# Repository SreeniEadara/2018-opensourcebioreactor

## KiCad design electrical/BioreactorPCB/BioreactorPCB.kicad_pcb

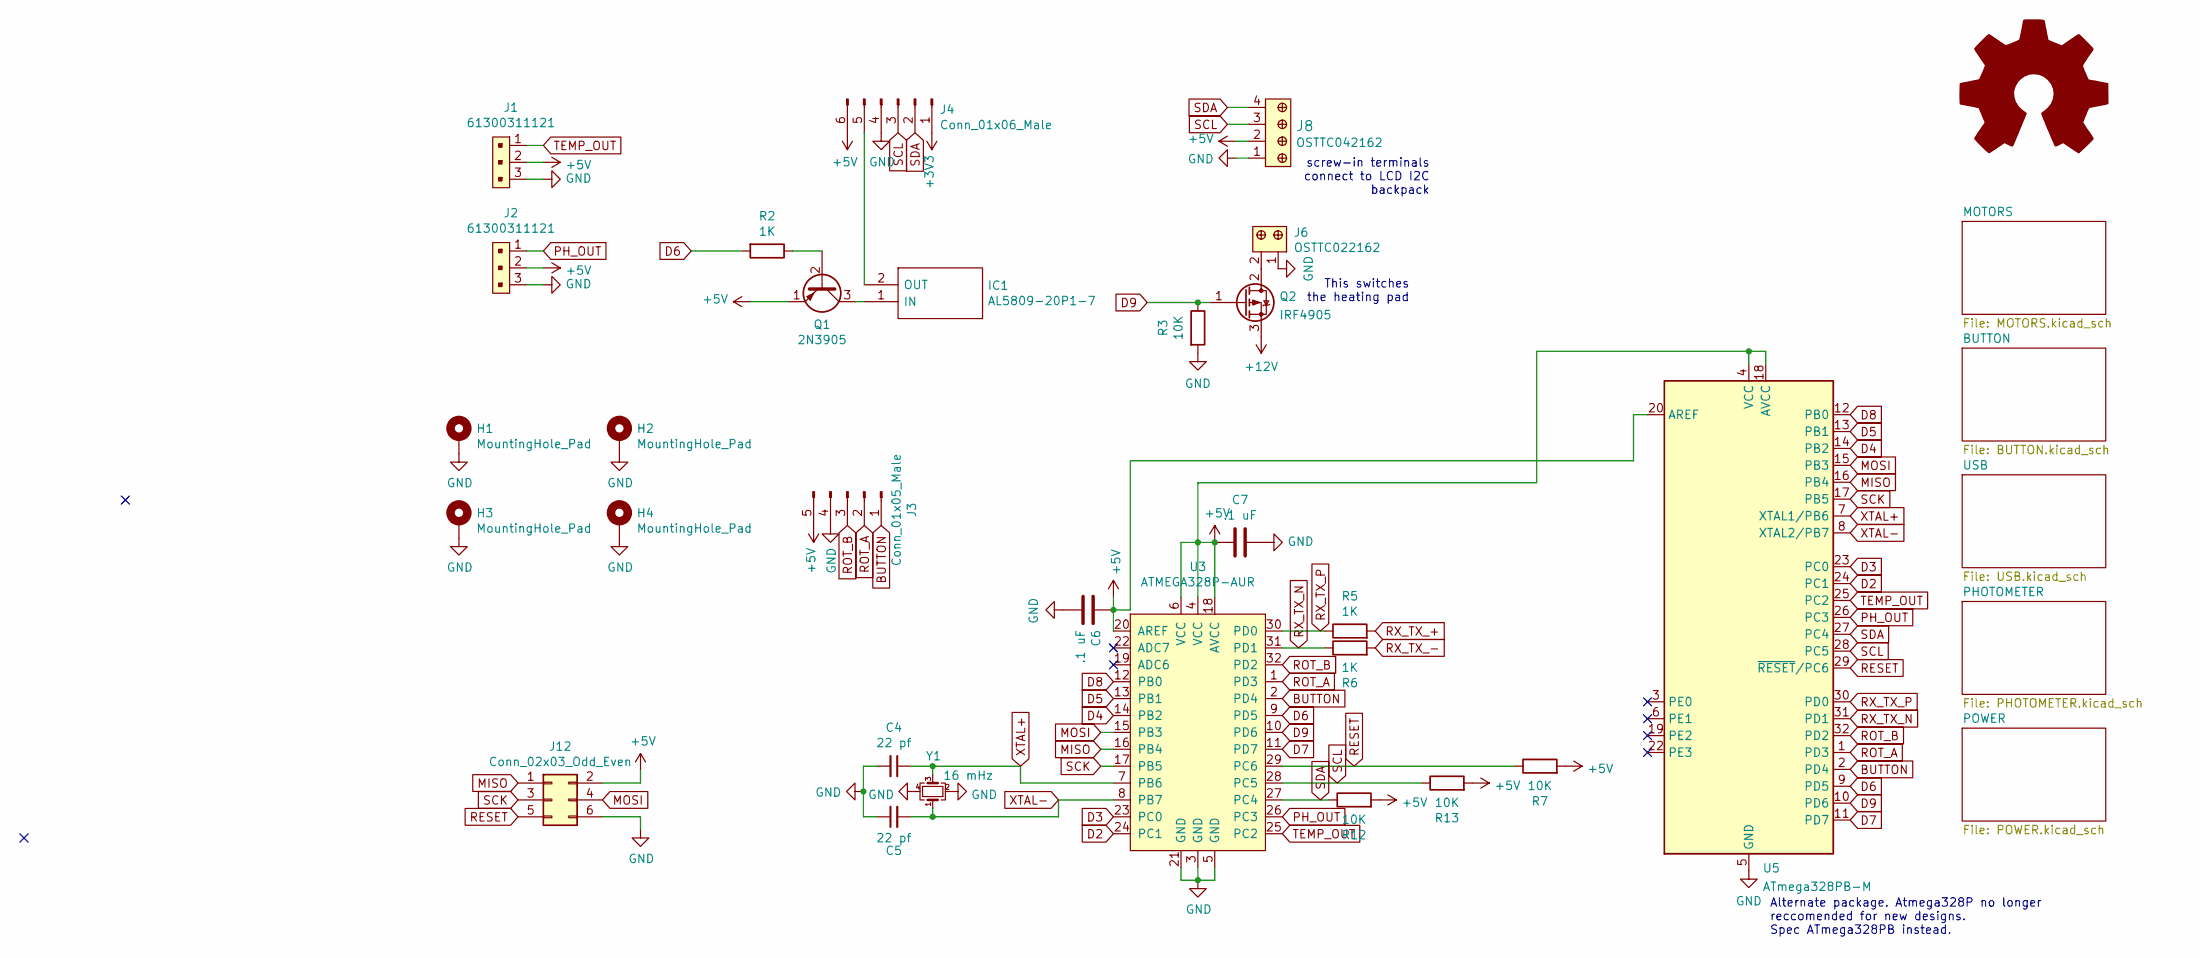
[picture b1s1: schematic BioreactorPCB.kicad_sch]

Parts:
C4, C5: 22 pf; C_0603_1608Metric_Pad1.08x0.95mm_HandSolder
C6, C7: .1 uF; C_0603_1608Metric_Pad1.08x0.95mm_HandSolder
H1, H2, H3, H4: MountingHole_Pad; MountingHole_3.2mm_M3_DIN965_Pad
IC1: AL5809-20P1-7; AL580920QP17; Manufacturer_Part_Number AL5809-20P1-7; Mouser Part Number 621-AL5809-20P1-7
J1, J2: 61300311121; PinHeader_1x3_P2.54_Drill1.1mm; MPN 61300311121; Digi-Key_PN 732-5316-ND
J3: Conn_01x05_Male; Molex_KK-254_AE-6410-05A_1x05_P2.54mm_Vertical
J4: Conn_01x06_Male; Molex_KK-254_AE-6410-06A_1x06_P2.54mm_Vertical
J6: OSTTC022162; Term_Block_1x2_P5.08MM; MPN OSTTC022162; Digi-Key_PN ED2609-ND
J8: OSTTC042162; Term_Block_1x4_P5.08mm; MPN OSTTC042162; Digi-Key_PN ED2611-ND
J12: Conn_02x03_Odd_Even; PinHeader_2x03_P2.54mm_Vertical
Q1: 2N3905; TO-92_Inline
Q2: IRF4905; TO-262-3_Vertical
R2, R5, R6: 1K; R_0805_2012Metric_Pad1.20x1.40mm_HandSolder
R3, R7, R12, R13: 10K; R_0805_2012Metric_Pad1.20x1.40mm_HandSolder
U3: ATMEGA328P-AUR; TQFP-32_7x7mm; MPN ATMEGA328P-AUR; Digi-Key_PN ATMEGA328P-AURCT-ND
U5: ATmega328PB-M; QFN-32-1EP_5x5mm_P0.5mm_EP3.1x3.1mm
Y1: 16 mHz; Crystal_SMD_3225-4Pin_3.2x2.5mm_HandSoldering

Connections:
+3V3: J4.1; also elsewhere on the board
+5V: C6.1, C7.2, J1.2, J2.2, J3.5, J4.6, J8.2, J12.2, Q1.1 (E), R7.2, R12.2, R13.2, U3.4 (VCC), U3.6 (VCC), U3.18 (AVCC), U3.20 (AREF), U5.4 (VCC), U5.18 (AVCC), U5.20 (AREF); also elsewhere on the board
+12V: Q2.3 (S); also elsewhere on the board
BUTTON: J3.1, U3.2 (PD4), U5.2 (PD4)
D2: U3.24 (PC1), U5.24 (PC1); also elsewhere on the board
D3: U3.23 (PC0), U5.23 (PC0); also elsewhere on the board
D4: U3.14 (PB2), U5.14 (PB2); also elsewhere on the board
D5: U3.13 (PB1), U5.13 (PB1); also elsewhere on the board
D6: R2.2, U3.9 (PD5), U5.9 (PD5)
D7: U3.11 (PD7), U5.11 (PD7); also elsewhere on the board
D8: U3.12 (PB0), U5.12 (PB0); also elsewhere on the board
D9: Q2.1 (G), R3.1, U3.10 (PD6), U5.10 (PD6)
GND: C4.2, C5.1, C6.2, C7.1, H1.1, H2.1, H3.1, H4.1, J1.3, J2.3, J3.4, J4.4, J6.1, J8.1, J12.6, R3.2, U3.3 (GND), U3.5 (GND), U3.21 (GND), U5.5 (GND), U5.21 (GND), U5.33 (GND), Y1.2, Y1.4; also elsewhere on the board
MISO: J12.1, U3.16 (PB4), U5.16 (PB4)
MOSI: J12.4, U3.15 (PB3), U5.15 (PB3)
unnamed: IC1.1 (IN), Q1.3 (C)
unnamed: IC1.2 (OUT), J4.5
unnamed: J6.2, Q2.2 (D)
unnamed: Q1.2 (B), R2.1
PH_OUT: J2.1, U3.26 (PC3), U5.26 (PC3)
RESET: J12.5, R7.1, U3.29 (PC6), U5.29 (~RESET/PC6); also elsewhere on the board
ROT_A: J3.2, U3.1 (PD3), U5.1 (PD3)
ROT_B: J3.3, U3.32 (PD2), U5.32 (PD2)
RX_TX_+: R5.2; also elsewhere on the board
RX_TX_-: R6.2; also elsewhere on the board
RX_TX_N: R6.1, U3.31 (PD1), U5.31 (PD1)
RX_TX_P: R5.1, U3.30 (PD0), U5.30 (PD0)
SCK: J12.3, U3.17 (PB5), U5.17 (PB5)
SCL: J4.3, J8.3, R13.1, U3.28 (PC5), U5.28 (PC5)
SDA: J4.2, J8.4, R12.1, U3.27 (PC4), U5.27 (PC4)
TEMP_OUT: J1.1, U3.25 (PC2), U5.25 (PC2)
XTAL+: C4.1, U3.7 (PB6), U5.7 (XTAL1/PB6), Y1.3
XTAL-: C5.2, U3.8 (PB7), U5.8 (XTAL2/PB7), Y1.1

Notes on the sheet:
This switches the heating pad
screw-in terminals connect to LCD I2C backpack
Alternate package. Atmega328P no longer reccomended for new designs. Spec ATmega328PB instead.

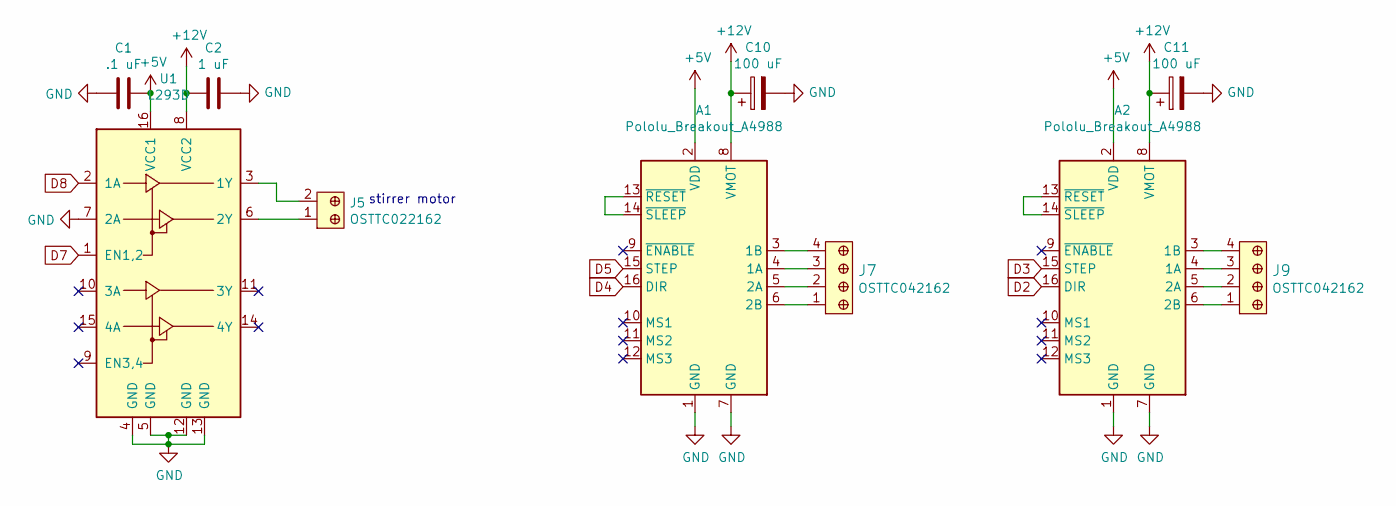
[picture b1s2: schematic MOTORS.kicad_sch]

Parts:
A1, A2: Pololu_Breakout_A4988; Pololu_Breakout-16_15.2x20.3mm
C1: .1 uF; C_0603_1608Metric_Pad1.08x0.95mm_HandSolder
C2: 1 uF; C_0603_1608Metric_Pad1.08x0.95mm_HandSolder
C10, C11: 100 uF; CP_Radial_D5.0mm_P2.50mm
J5: OSTTC022162; Term_Block_1x2_P5.08MM; MPN OSTTC022162; Digi-Key_PN ED2609-ND
J7, J9: OSTTC042162; Term_Block_1x4_P5.08mm; MPN OSTTC042162; Digi-Key_PN ED2611-ND
U1: L293D; DIP-16_W7.62mm

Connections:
+5V: A1.2 (VDD), A2.2 (VDD), C1.1, U1.16 (VCC1); also elsewhere on the board
+12V: A1.8 (VMOT), A2.8 (VMOT), C2.2, C10.1, C11.1, U1.8 (VCC2); also elsewhere on the board
D2: A2.16 (DIR); also elsewhere on the board
D3: A2.15 (STEP); also elsewhere on the board
D4: A1.16 (DIR); also elsewhere on the board
D5: A1.15 (STEP); also elsewhere on the board
D7: U1.1 (EN1,2); also elsewhere on the board
D8: U1.2 (1A); also elsewhere on the board
GND: A1.1 (GND), A1.7 (GND), A2.1 (GND), A2.7 (GND), C1.2, C2.1, C10.2, C11.2, U1.4 (GND), U1.5 (GND), U1.7 (2A), U1.12 (GND), U1.13 (GND); also elsewhere on the board
unnamed: A1.3 (1B), J7.4
unnamed: A1.4 (1A), J7.3
unnamed: A1.5 (2A), J7.2
unnamed: A1.6 (2B), J7.1
unnamed: A1.13 (~RESET), A1.14 (~SLEEP)
unnamed: A2.3 (1B), J9.4
unnamed: A2.4 (1A), J9.3
unnamed: A2.5 (2A), J9.2
unnamed: A2.6 (2B), J9.1
unnamed: A2.13 (~RESET), A2.14 (~SLEEP)
unnamed: J5.1, U1.6 (2Y)
unnamed: J5.2, U1.3 (1Y)

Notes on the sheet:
stirrer motor

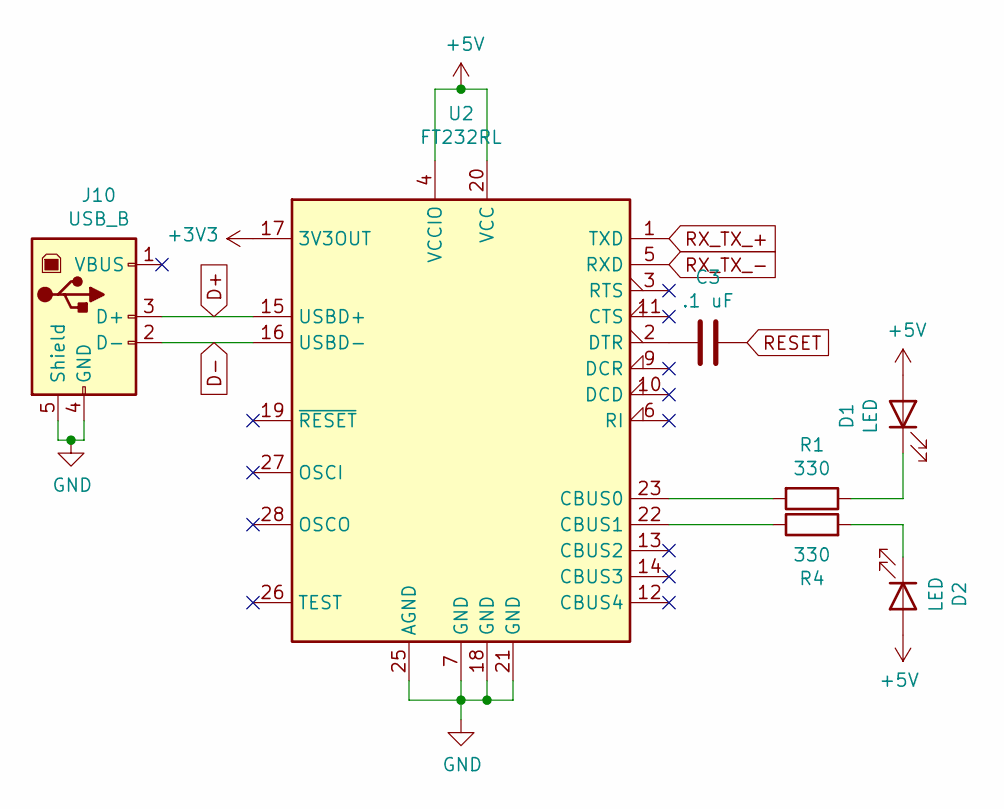
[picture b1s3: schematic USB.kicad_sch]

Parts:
C3: .1 uF; C_0603_1608Metric_Pad1.08x0.95mm_HandSolder
D1, D2: LED; LED_D5.0mm
J10: USB_B; USB_B_Lumberg_2411_02_Horizontal
R1, R4: 330; R_0805_2012Metric_Pad1.20x1.40mm_HandSolder
U2: FT232RL; SSOP-28_5.3x10.2mm_P0.65mm

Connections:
+3V3: U2.17 (3V3OUT); also elsewhere on the board
+5V: D1.2 (A), D2.2 (A), U2.4 (VCCIO), U2.20 (VCC); also elsewhere on the board
D+: J10.3 (D+), U2.15 (USBD+)
D-: J10.2 (D-), U2.16 (USBD-)
GND: J10.4 (GND), J10.5 (Shield), U2.7 (GND), U2.18 (GND), U2.21 (GND), U2.25 (AGND); also elsewhere on the board
unnamed: C3.2, U2.2 (DTR)
unnamed: D1.1 (K), R1.1
unnamed: D2.1 (K), R4.2
unnamed: R1.2, U2.23 (CBUS0)
unnamed: R4.1, U2.22 (CBUS1)
RESET: C3.1; also elsewhere on the board
RX_TX_+: U2.1 (TXD); also elsewhere on the board
RX_TX_-: U2.5 (RXD); also elsewhere on the board

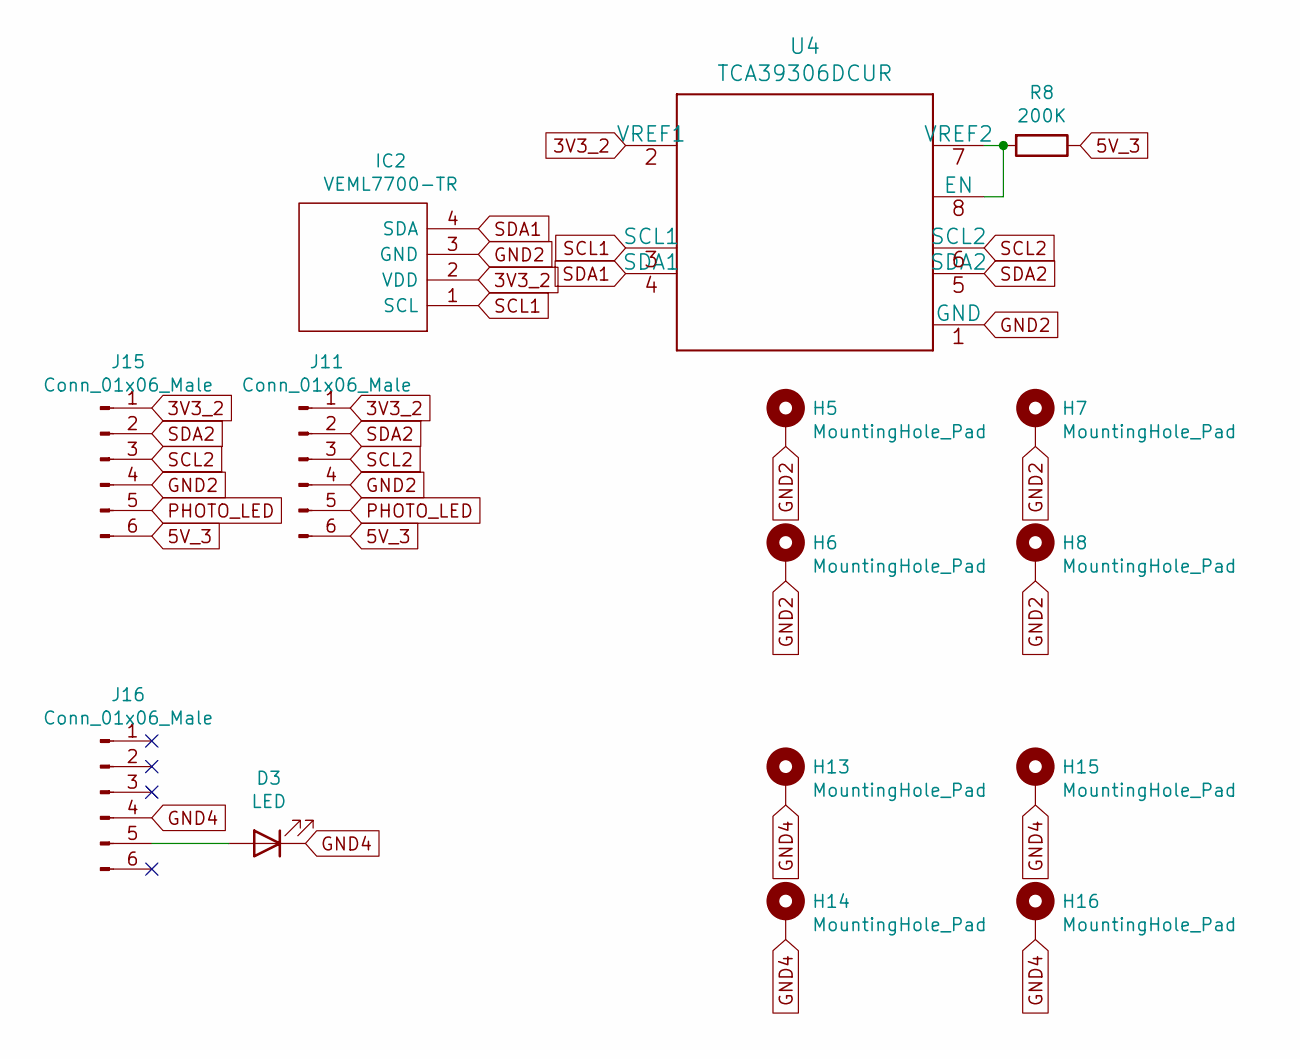
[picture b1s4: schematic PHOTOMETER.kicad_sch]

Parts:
D3: LED; LED_D5.0mm
H5, H6, H7, H8, H13, H14, H15, H16: MountingHole_Pad; MountingHole_3.2mm_M3_DIN965_Pad
IC2: VEML7700-TR; VEML7700; Manufacturer_Part_Number VEML7700-TR; Mouser Part Number 78-VEML7700-TR
J11, J15, J16: Conn_01x06_Male; Molex_KK-254_AE-6410-06A_1x06_P2.54mm_Vertical
R8: 200K; R_0805_2012Metric_Pad1.20x1.40mm_HandSolder
U4: TCA39306DCUR

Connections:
3V3_2: IC2.2 (VDD), J11.1, J15.1, U4.2 (VREF1)
5V_3: J11.6, J15.6, R8.1
GND2: H5.1, H6.1, H7.1, H8.1, IC2.3 (GND), J11.4, J15.4, U4.1 (GND)
GND4: D3.1 (K), H13.1, H14.1, H15.1, H16.1, J16.4
unnamed: D3.2 (A), J16.5
unnamed: R8.2, U4.7 (VREF2), U4.8 (EN)
PHOTO_LED: J11.5, J15.5
SCL1: IC2.1 (SCL), U4.3 (SCL1)
SCL2: J11.3, J15.3, U4.6 (SCL2)
SDA1: IC2.4 (SDA), U4.4 (SDA1)
SDA2: J11.2, J15.2, U4.5 (SDA2)

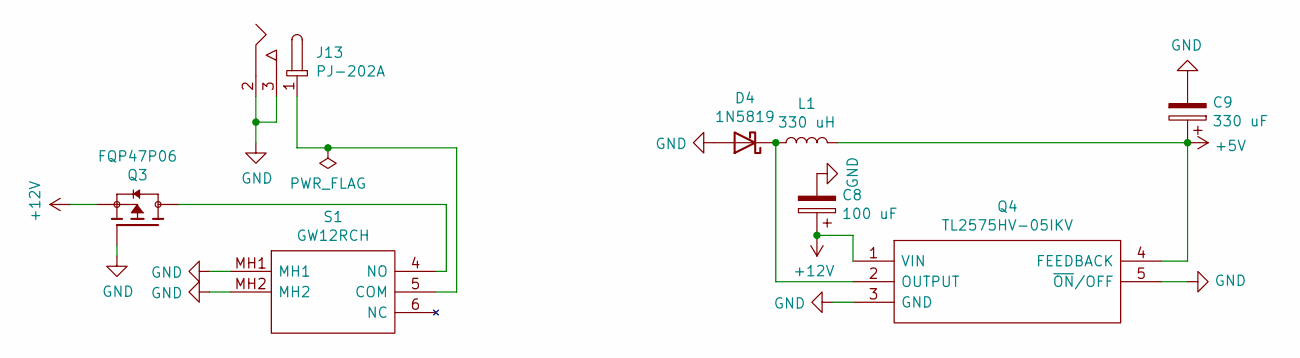
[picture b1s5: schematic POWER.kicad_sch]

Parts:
C8: 100 uF; CP_Radial_D5.0mm_P2.50mm
C9: 330 uF; CP_Radial_D5.0mm_P2.50mm
D4: 1N5819; D_DO-41_SOD81_P10.16mm_Horizontal
J13: PJ-202A; Barrel_Jack_5.5mmODx2.1mmID_PJ-202A; MPN PJ-202A; Digi-Key_PN CP-202A-ND
L1: 330 uH; L_Bourns_SRR1210A
Q3: FQP47P06; TO-220-3_Vertical
Q4: TL2575HV-05IKV; TO-220-5_P3.4x3.7mm_StaggerEven_Lead3.8mm_Vertical; Manufacturer_Part_Number TL2575HV-05IKV; Mouser Part Number 595-TL2575HV-05IKV
S1: GW12RCH; Manufacturer_Part_Number GW12RCH; Mouser Part Number 633-GW12RCH

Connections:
+5V: C9.1, L1.2, Q4.4 (FEEDBACK); also elsewhere on the board
+12V: C8.1, Q3.3, Q4.1 (VIN); also elsewhere on the board
GND: C8.2, C9.2, D4.2 (A), J13.2, J13.3, Q3.1, Q4.3 (GND), Q4.5 (~ON/OFF), S1.MH1, S1.MH2; also elsewhere on the board
unnamed: D4.1 (K), L1.1, Q4.2 (OUTPUT)
unnamed: J13.1, S1.5 (COM)
unnamed: Q3.2, S1.4 (NO)

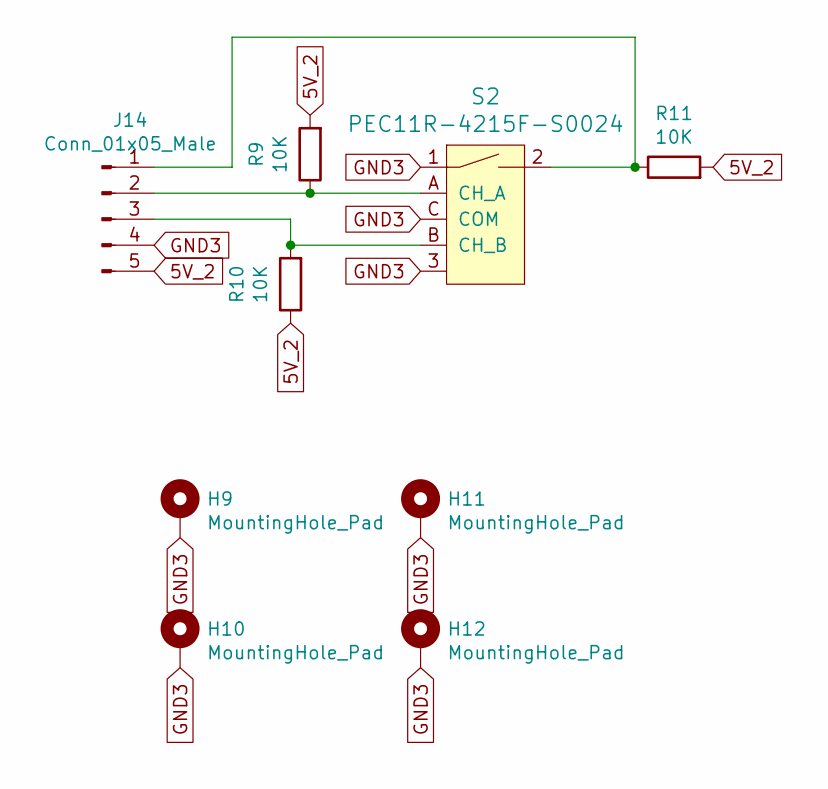
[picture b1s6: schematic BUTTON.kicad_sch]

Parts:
H9, H10, H11, H12: MountingHole_Pad; MountingHole_3.2mm_M3_DIN965_Pad
J14: Conn_01x05_Male; Molex_KK-254_AE-6410-05A_1x05_P2.54mm_Vertical
R9, R10, R11: 10K; R_0805_2012Metric_Pad1.20x1.40mm_HandSolder
S2: PEC11R-4215F-S0024; Rotary_Encoder_Switched_PEC11R; MPN PEC11R-4215F-S0024; Digi-Key_PN PEC11R-4215F-S0024-ND

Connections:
5V_2: J14.5, R9.2, R10.1, R11.2
GND3: H9.1, H10.1, H11.1, H12.1, J14.4, S2.1, S2.3, S2.C (COM)
unnamed: J14.1, R11.1, S2.2
unnamed: J14.2, R9.1, S2.A (CH_A)
unnamed: J14.3, R10.2, S2.B (CH_B)

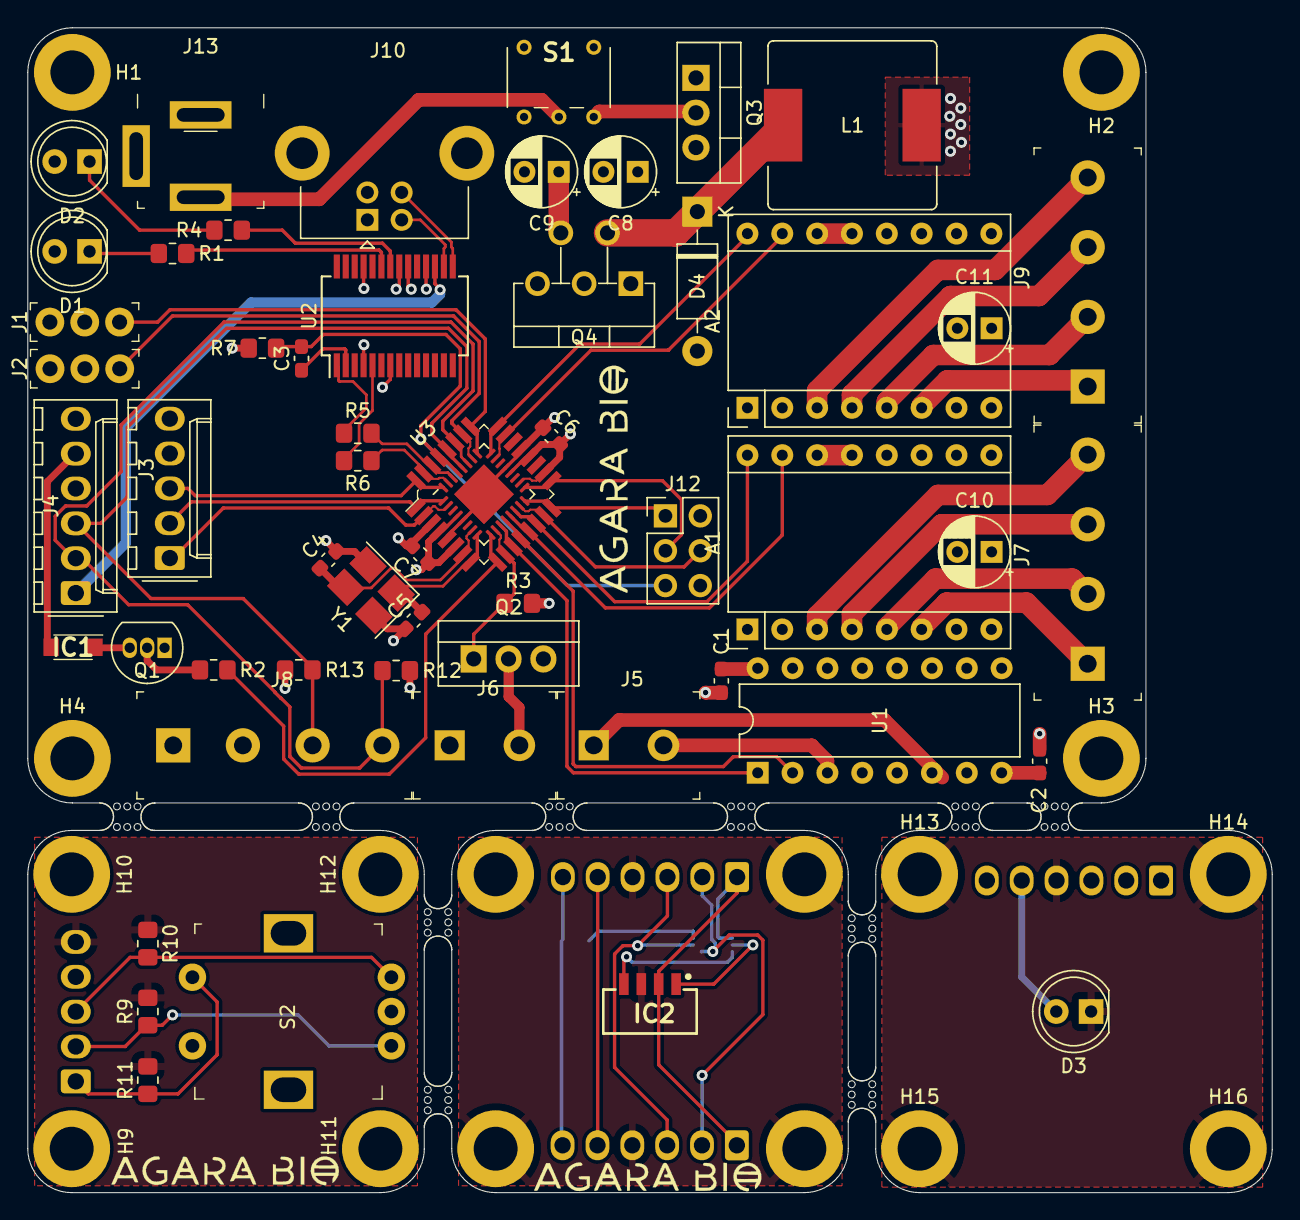
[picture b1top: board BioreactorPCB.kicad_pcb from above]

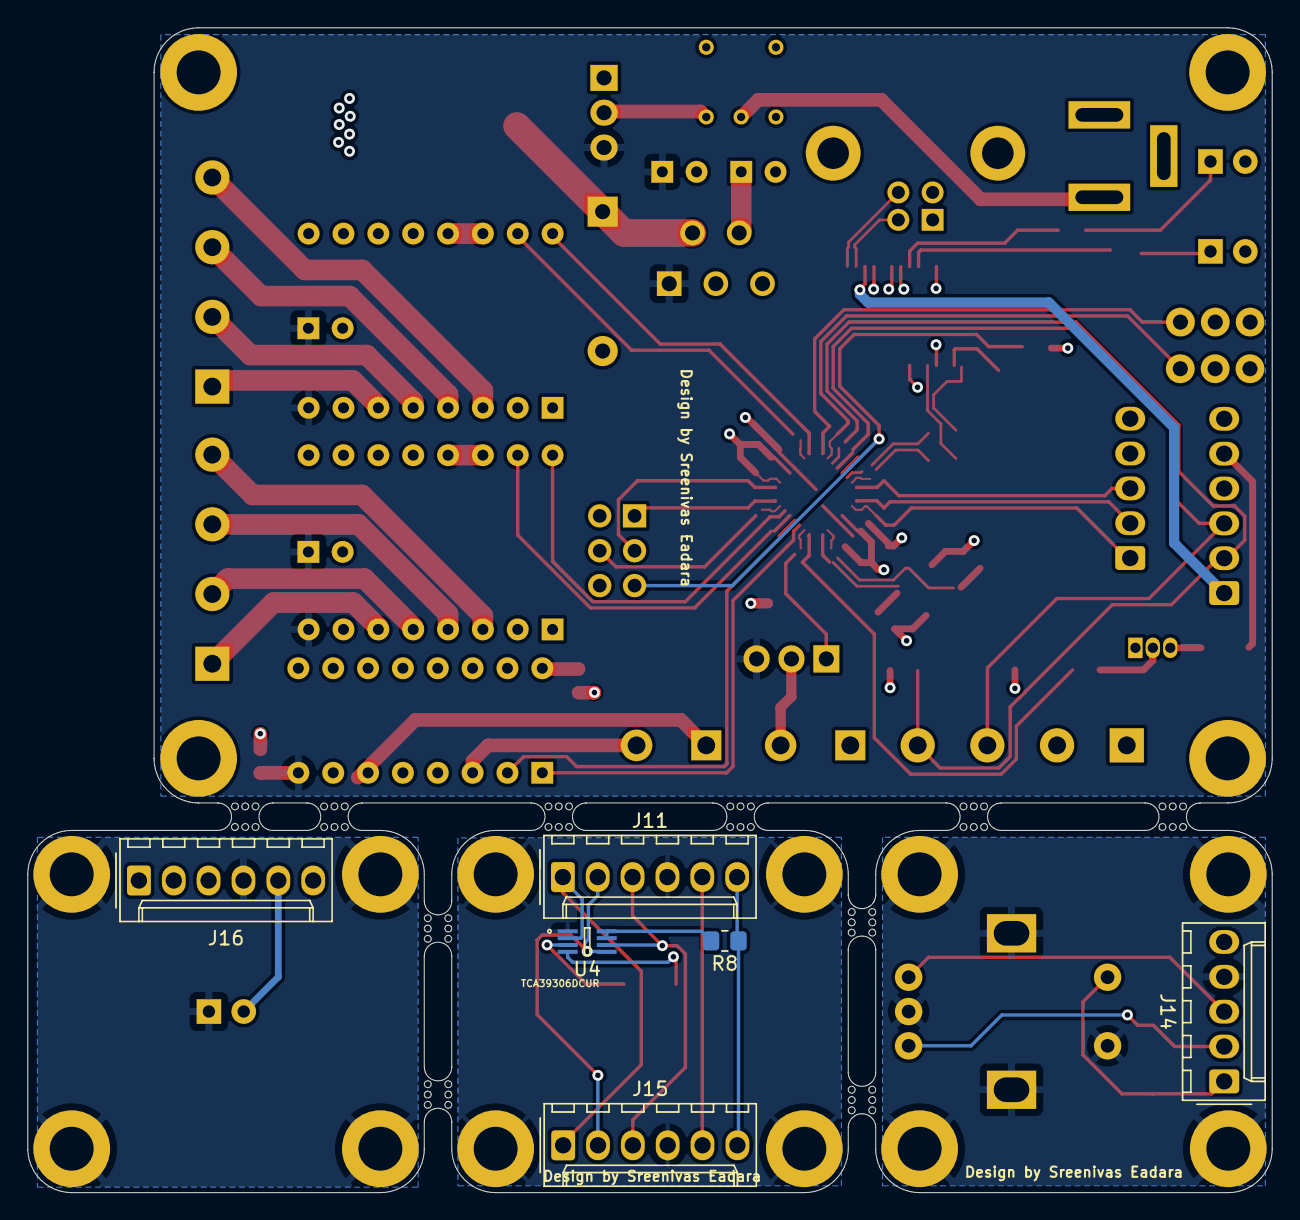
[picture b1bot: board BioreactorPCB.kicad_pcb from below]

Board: 4 copper layers, 90.7 x 84.9 mm, 87 parts (6 on the bottom side), 71 nets.

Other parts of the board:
mouse-bite-2mm-slot, mouse-bite-2mm-slot#2, mouse-bite-2mm-slot#3, mouse-bite-2mm-slot#4, mouse-bite-2mm-slot#5, mouse-bite-2mm-slot#6, mouse-bite-2mm-slot#7, mouse-bite-2mm-slot#8, mouse-bite-2mm-slot#9, mouse-bite-2mm-slot#10: VAL**; mouse-bite-2mm-slot

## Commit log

2021-04-17 Adding Agara Bio PCB design for bioreactor and flow-through photometer. ~Designed by Sreenivas Eadara~
2021-10-21 Arduino code is validated and working on Arduino Nano Every and board layout updated to match latest.
2021-10-21 Added .STEP and .STL files designed by James Li
2022-01-01 PCB rev 2.0 development underway
2022-01-02 another intermediate
2022-01-02 Rev 2.0 schematic ready
2022-01-02 updates WIP to v 2.0
2022-01-03 Completed rev 2.0 schematic for real now
2022-01-04 added missing electrolytic capacitors for A4988 breakouts. Preliminary layout now in place
2022-01-05 motherboard layout complete.
2022-01-05 moved a couple traces
2022-01-05 Converted all nonpolarized resistors and capacitors to SMD. USB now has differential pairs that conform to design guidelines. Lots of traces, to what end? idk.
2022-01-05 literally just moved some labels
2022-01-05 More routing changes for greater plane continuity
2022-01-05 Moved around some traces for better planes
2022-01-06 finished daughterboards
2022-01-06 panelized completed daughterboards and added clearance of planes to board edge
2022-01-06 added silk labels
2022-01-08 changed layout and schematic to reflect addition of a third daughterboard and separation of the LED and photodiode onto separate boards
2022-01-10 Updated BOM with cables and DigiKey PNs
2022-02-07 Added 10K pullups on the i2c SDA and SCL. Apparently AVR internal pullups are too weak! Oops.
2022-02-07 cleanup of tracks and plane
2022-02-23 Added alternate Atmega328PB 32QFN package and rerouted board to match
2022-02-23 some track cleanup
2022-02-24 many improvements to ground plane at some expense to 5V plane
2022-02-25 Removed vias in pad (so sad to see them go, but I'm not made of money) and set min track width and spacing to 6 mil
2022-02-26 Replaced through-hole crystal with SMD package and moved capacitors so they actually decouple the MCU
2022-02-26 changed MOSFET to PFET and made the heater switched by a high-side switch
2022-03-11 NOW a 4-layer pCB with drastically improved routing
2022-03-11 +12V is now bottom copper plane
2022-03-21 increeased stepper motor trace width. Miscellaneous improvements

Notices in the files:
parts and their libraries:
Copyright 2021 Accelerated Designs. All rights reserved.
